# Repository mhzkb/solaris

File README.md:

# Solaris - W.I.P.
Katana staggered 34 key mechanical keyboard with support for trackball sensor breakout board or rotary encoders.

### TODO
- Adjust sensor position
- Add mounting cutouts
- Adjust silk screen
- Possibly convert to integrated MCU and sensor circuit
- Finish proto case
- Design final case

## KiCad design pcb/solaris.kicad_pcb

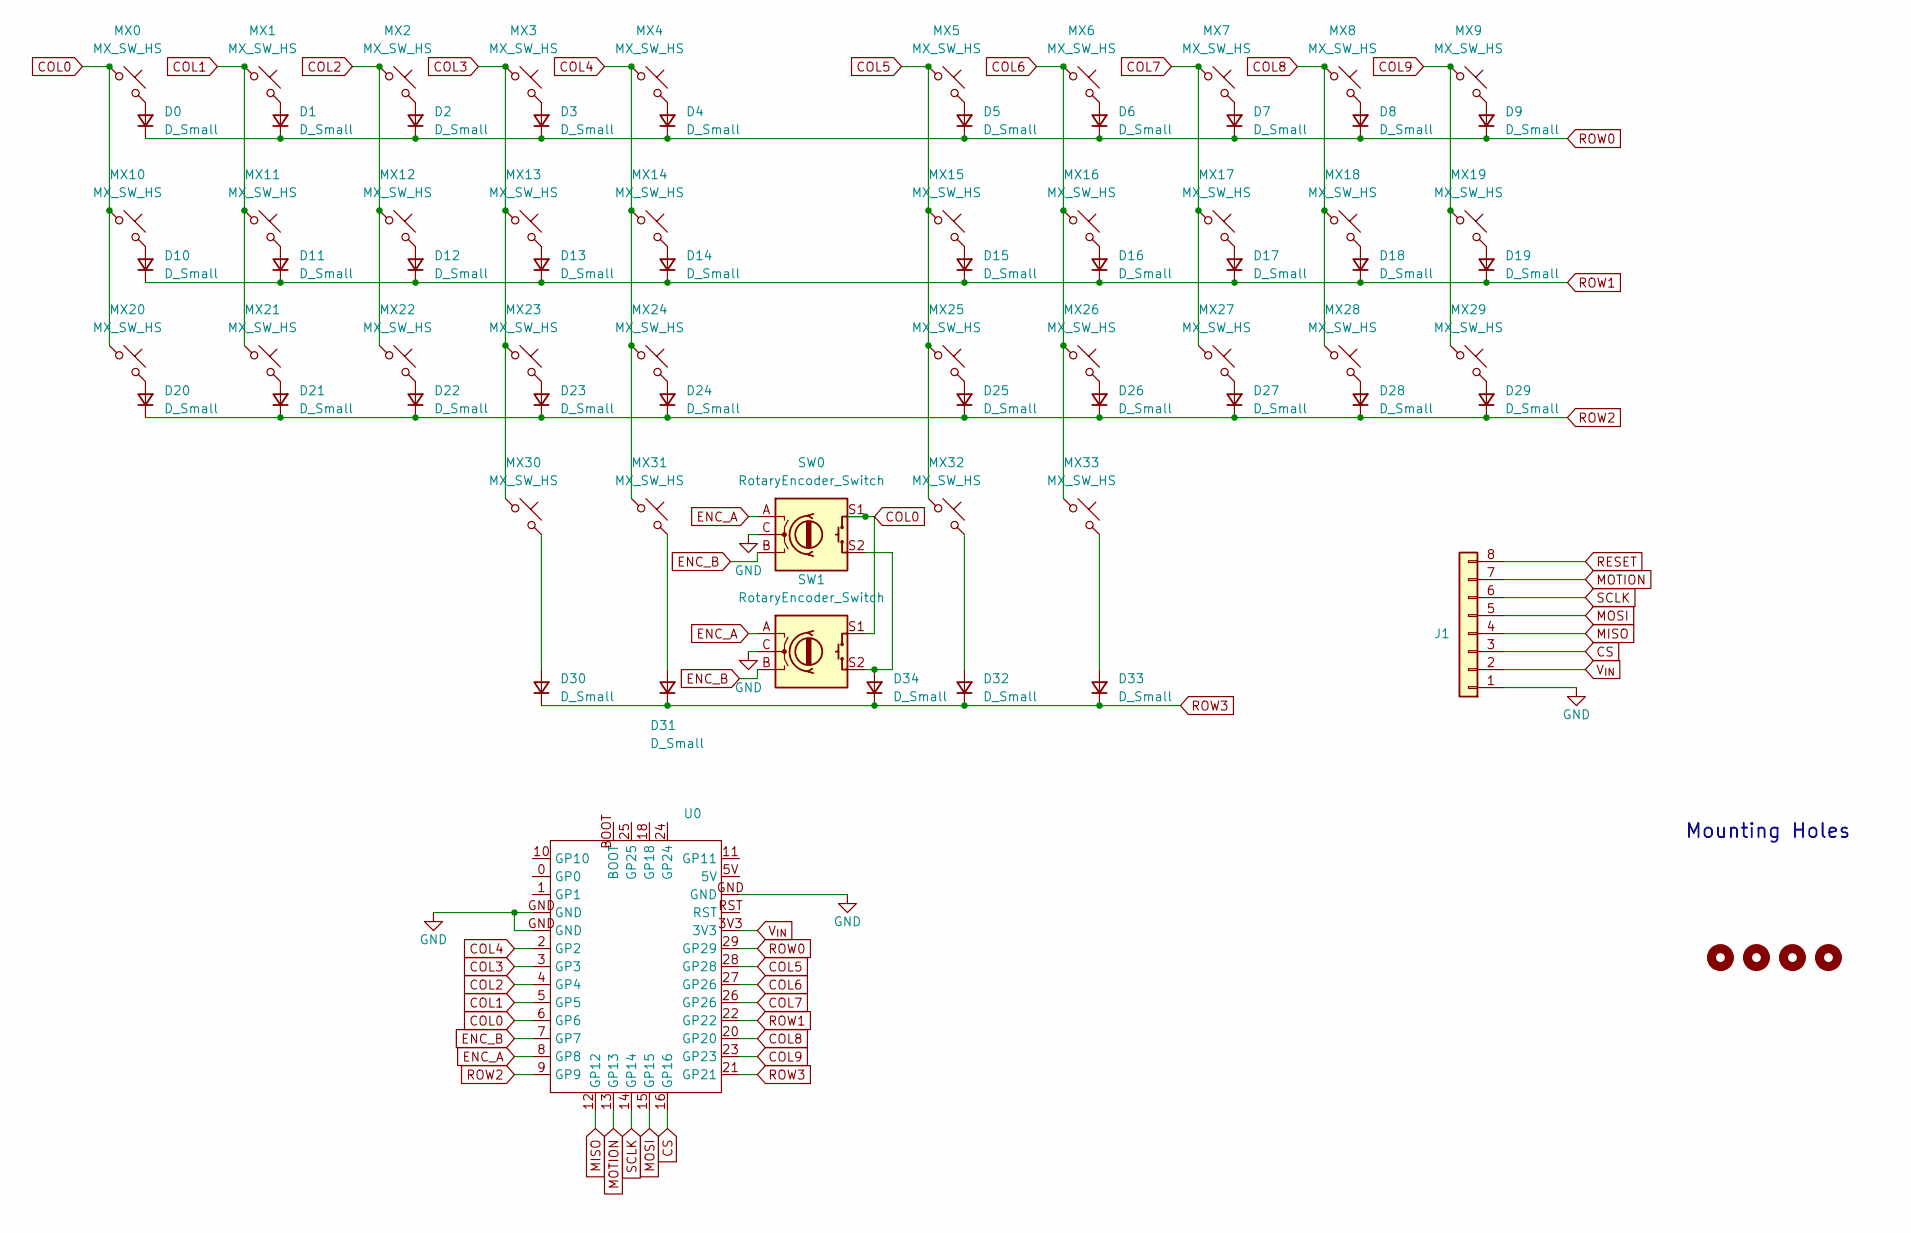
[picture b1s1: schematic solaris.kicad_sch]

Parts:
D0, D1, D2, D3, D4, D5, D6, D7, D8, D9, D10, D11, D12, D13, D14, D15, D16, D17, D18, D19, D20, D21, D22, D23, D24, D25, D26, D27, D28, D29, D30, D31, D32, D33, D34: D_Small; D_SOD-123
H1, H2, H3, H4: MountingHole_Pad; MountingHole_3.2mm_M3_ISO14580
J1: Conn_01x08; PinHeader_1x08_P2.54mm_Vertical
MX0, MX1, MX2, MX3, MX4, MX5, MX6, MX7, MX8, MX9, MX10, MX11, MX12, MX13, MX14, MX15, MX16, MX17, MX18, MX19, MX20, MX21, MX22, MX23, MX24, MX25, MX26, MX27, MX28, MX29: MX_SW_HS; SW_MX_HS_CPG151101S11_1u
MX30, MX33: MX_SW_HS; SW_MX_HS_CPG151101S11_1.25u
MX31, MX32: MX_SW_HS; SW_MX_HS_CPG151101S11_1.75u
SW0: RotaryEncoder_Switch; RotaryEncoder_EC11-no-legs
SW1: RotaryEncoder_Switch; EVQWGD001
U0: pro_micro_rp2040

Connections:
COL0: MX0.1, MX10.1, MX20.1, SW0.S1, SW1.S1, U0.6 (GP6)
COL1: MX1.1, MX11.1, MX21.1, U0.5 (GP5)
COL2: MX2.1, MX12.1, MX22.1, U0.4 (GP4)
COL3: MX3.1, MX13.1, MX23.1, MX30.1, U0.3 (GP3)
COL4: MX4.1, MX14.1, MX24.1, MX31.1, U0.2 (GP2)
COL5: MX5.1, MX15.1, MX25.1, MX32.1, U0.28 (GP28)
COL6: MX6.1, MX16.1, MX26.1, MX33.1, U0.27 (GP26)
COL7: MX7.1, MX17.1, MX27.1, U0.26 (GP26)
COL8: MX8.1, MX18.1, MX28.1, U0.20 (GP20)
COL9: MX9.1, MX19.1, MX29.1, U0.23 (GP23)
CS: J1.3, U0.16 (GP16)
ENC_A: SW0.A, SW1.A, U0.8 (GP8)
ENC_B: SW0.B, SW1.B, U0.7 (GP7)
GND: J1.1, SW0.C, SW1.C, U0.GND
MISO: J1.4, U0.12 (GP12)
MOSI: J1.5, U0.15 (GP15)
MOTION: J1.7, U0.13 (GP13)
unnamed: D0.2 (A), MX0.2
unnamed: D1.2 (A), MX1.2
unnamed: D2.2 (A), MX2.2
unnamed: D3.2 (A), MX3.2
unnamed: D4.2 (A), MX4.2
unnamed: D5.2 (A), MX5.2
unnamed: D6.2 (A), MX6.2
unnamed: D7.2 (A), MX7.2
unnamed: D8.2 (A), MX8.2
unnamed: D9.2 (A), MX9.2
unnamed: D10.2 (A), MX10.2
unnamed: D11.2 (A), MX11.2
unnamed: D12.2 (A), MX12.2
unnamed: D13.2 (A), MX13.2
unnamed: D14.2 (A), MX14.2
unnamed: D15.2 (A), MX15.2
unnamed: D16.2 (A), MX16.2
unnamed: D17.2 (A), MX17.2
unnamed: D18.2 (A), MX18.2
unnamed: D19.2 (A), MX19.2
unnamed: D20.2 (A), MX20.2
unnamed: D21.2 (A), MX21.2
unnamed: D22.2 (A), MX22.2
unnamed: D23.2 (A), MX23.2
unnamed: D24.2 (A), MX24.2
unnamed: D25.2 (A), MX25.2
unnamed: D26.2 (A), MX26.2
unnamed: D27.2 (A), MX27.2
unnamed: D28.2 (A), MX28.2
unnamed: D29.2 (A), MX29.2
unnamed: D30.2 (A), MX30.2
unnamed: D31.2 (A), MX31.2
unnamed: D32.2 (A), MX32.2
unnamed: D33.2 (A), MX33.2
unnamed: D34.2 (A), SW0.S2, SW1.S2
RESET: J1.8
ROW0: D0.1 (K), D1.1 (K), D2.1 (K), D3.1 (K), D4.1 (K), D5.1 (K), D6.1 (K), D7.1 (K), D8.1 (K), D9.1 (K), U0.29 (GP29)
ROW1: D10.1 (K), D11.1 (K), D12.1 (K), D13.1 (K), D14.1 (K), D15.1 (K), D16.1 (K), D17.1 (K), D18.1 (K), D19.1 (K), U0.22 (GP22)
ROW2: D20.1 (K), D21.1 (K), D22.1 (K), D23.1 (K), D24.1 (K), D25.1 (K), D26.1 (K), D27.1 (K), D28.1 (K), D29.1 (K), U0.9 (GP9)
ROW3: D30.1 (K), D31.1 (K), D32.1 (K), D33.1 (K), D34.1 (K), U0.21 (GP21)
SCLK: J1.6, U0.14 (GP14)
V_{IN}: J1.2, U0.3V3

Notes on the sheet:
Mounting Holes

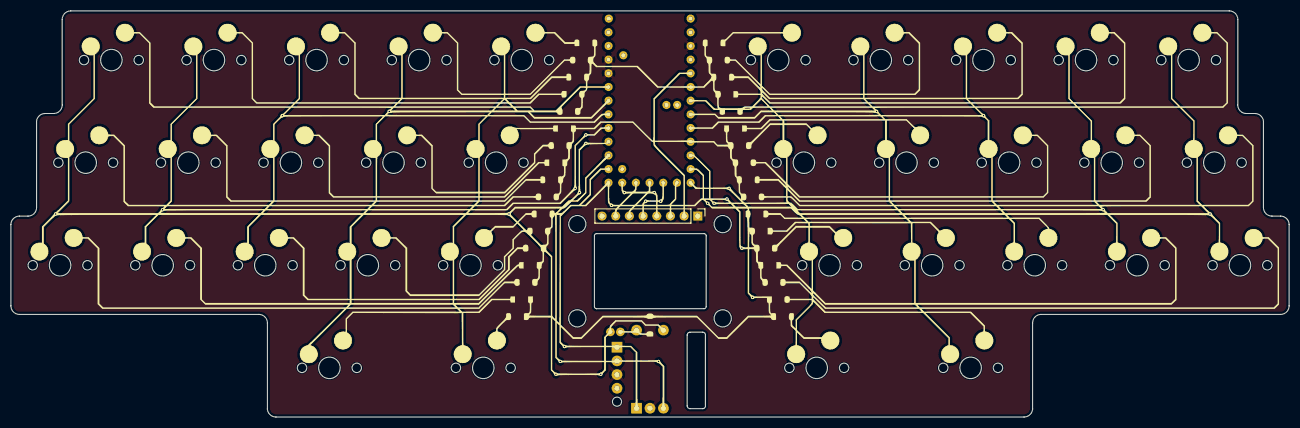
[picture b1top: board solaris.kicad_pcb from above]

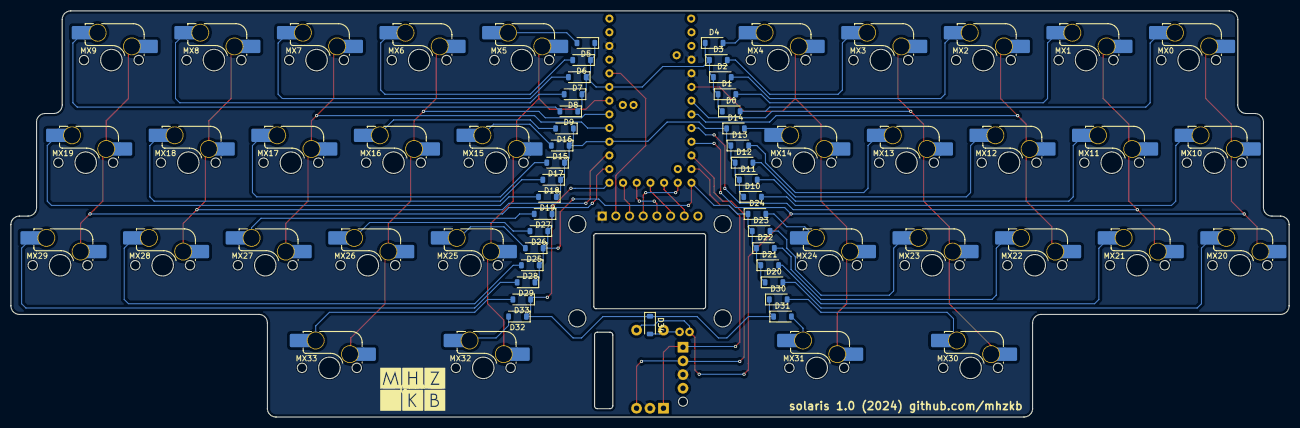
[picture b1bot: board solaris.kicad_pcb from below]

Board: 2 copper layers, 237.3 x 75.4 mm, 77 parts (73 on the bottom side), 58 nets.

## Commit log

2025-02-26 Added README
2025-10-24 Added Kicad project and export files
